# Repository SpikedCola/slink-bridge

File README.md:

# slink-bridge

A web interface for my Sony STR-DB930 home theater receiver that runs on an ESP32. It communicates over S-Link (on the Control A1 jack). 

The web interface shows power, current input and status, with buttons for inputs, volume, mute, 5.1 and more. 

## Tested on

| Board | Receiver | Pins (TX / RX) |
|---|---|---|
| LOLIN ESP32-S2 Mini v1.0.0 | Sony STR-DB930 | GPIO16 / GPIO18 |
| ESP32-C3 SuperMini | Sony STR-DB930 | GPIO3 / GPIO4 |

## Credits

- [boehmel.de S-Link page](http://web.archive.org/web/20180831072659/http://boehmel.de/slink.htm): the S-Link / Control A1
  command and reply reference. The input codes, status queries, tuner, surround and settings commands all come from here.
- [robho/sony_slink](https://github.com/robho/sony_slink): bus timing (sync, bit and gap lengths) and
  the NPN open-collector transmit circuit, from their Arduino/ESP8266 sketches.
- [Reza's S-Link notes](http://web.archive.org/web/20070720171202/http://www.reza.net/slink/text.txt): background on driving the
  bus through a transistor, linked from robho/sony_slink.

## PCB

The PCB is a simple carrier board that goes on the back of an ESP32-C3 SuperMini. A 1/8" mono jack connects to the receiver.

### Schematic

The receiver pulls the bus up to ~5 V. To transmit a pulse, we turn Q1 on, which pulls the bus to ground. 

To receive, the diode lets the bus go low, but blocks the 5 V idle level from making it to the ESP32 which only has 3.3v IO.

The part values are not critical.

### Board

The outline of the board cuts the 0.1" header, resulting in castellations that can be soldered to the SuperMini's 0.1" header.

### Observations After Building

- The sample PCBs were made 1.6mm thick, I would probably go thinner.
- I didn't pay for the castellation option, and the cut header was a little rough but worked just fine.
- The holes to pass the cable through for strain relief didn't work as expected - the cable causes the board not to sit flat. Didn't end up using them.

## Winamp Plugin

This was the ultimate goal of the project - an easy interface to switch between Computer and TV sources.

The plugin adds a small window with buttons to switch between sources.

## Firmware

The ESP32 runs `WebServer.h` which displays a single page with HTML/CSS/JS.

This has been tested with two ESP32 boards, `s2mini` (LOLIN ESP32-S2 Mini) and `c3supermini` (ESP32-C3 SuperMini). The prototype PCBs are meant to work with the SuperMini.

Each board's pins are in `include/board.h`.

The interface is accessible at `http://<ip>`, and `http://slink.local` if mDNS is supported.

### Software Requirements

```
sudo apt install -y pipx
pipx install platformio
pipx ensurepath
sudo usermod -aG dialout $USER # only if flashing over USB from Linux - I used web.esphome.io
```

### Setup

- Copy `include/secrets.h.example` to `include/secrets.h` and `secrets.ini.example` to `secrets.ini`, and fill them in. Make up a secret, and fill your wifi details.
- Run `pio run -e c3supermini` in the `firmware` directory. This writes `firmware/slink-bridge-c3supermini-full.bin` which can be uploaded on web.esphome.io
- Subsequent updates can be sent over wifi: `pio run -e s2mini_ota -t upload --upload-port <ip>`

### Talking to it

```
curl http://slink.local/status
curl 'http://slink.local/log?since=0'
curl -X POST 'http://slink.local/send?hex=c06a'  # ask the amplifier its name
curl 'http://slink.local/debug?on=1'        # log raw pulse widths too
nc slink.local 23                            # live log, type hex to send
```

Log lines are `seq millis RX|TX hex`. `RX` is traffic from the receiver.

### STR-DB930 protocol

See [Credits](#credits) for sources.

Commands go to device `c0`. The receiver answers from `c8` (and `c9`/`cb`).

| Send | Meaning | Reply |
|------|---------|-------|
| `c00f` | query current source | `c870 AA VV ..` (AA audio source, VV video source) |
| `c05004` | select MD/DAT | `c870041601b0`, `cb700b003400` |
| `c05016` | select TV | `c870161601ff`, `cb7001003400` |
| `c06a` | query name | `c86a` + "STR-DB930 " |
| `c02e` / `c02f` | power on / off | `c82e` / `c82f` |

The receiver sends messages unprompted, including on startup, and on every input change (including turning the front panel input knob).
Turning the volume knob is not reported, so we can only drive volume up and down, not to a specific location.

## Case

The case design is based on the [Ultra-Compact Case for ESP32-C3 SuperMini on Thingiverse](https://www.thingiverse.com/thing:7420590). I closed the holes in the base, made the box deeper, and added a cutout for the PCB and wire to enter.

## Assembly Photos

#### Soldering the components

#### Ready to be assembled

#### Cable soldered

#### Board soldered to ESP32

#### Board installed in case

#### The completed assembly

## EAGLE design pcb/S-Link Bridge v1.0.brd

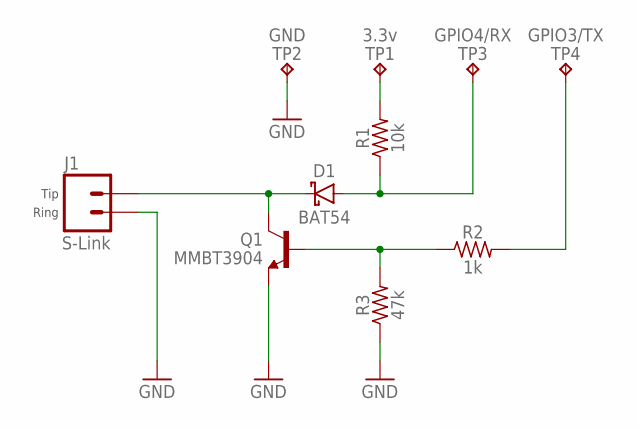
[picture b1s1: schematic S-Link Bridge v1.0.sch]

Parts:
D1: BAT54; SOD-123
J1: S-Link; 1X02
Q1: MMBT3904; SOT23
R1: 10k; R0603
R2: 1k; R0603
R3: 47k; R0603
TP1: 3.3v; P1-10
TP2: GND; P1-10
TP3: GPIO4/RX; P1-10
TP4: GPIO3/TX; P1-10

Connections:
GND: J1.2, Q1.2 (E), R3.1, TP2.TP
unnamed: D1.C, J1.1, Q1.3 (C)
unnamed: D1.A, R1.1, TP3.TP
unnamed: R1.2, TP1.TP
unnamed: Q1.1 (B), R2.1, R3.2
unnamed: R2.2, TP4.TP

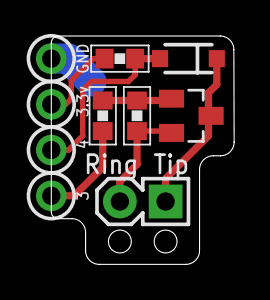
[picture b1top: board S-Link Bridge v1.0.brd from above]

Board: 2 copper layers, 10.2 x 12.7 mm, 10 parts (0 on the bottom side), 6 nets.
